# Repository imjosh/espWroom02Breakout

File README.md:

# espWroom02Breakout
Breakout board for the ESPWROOM02 Esp8266 Module

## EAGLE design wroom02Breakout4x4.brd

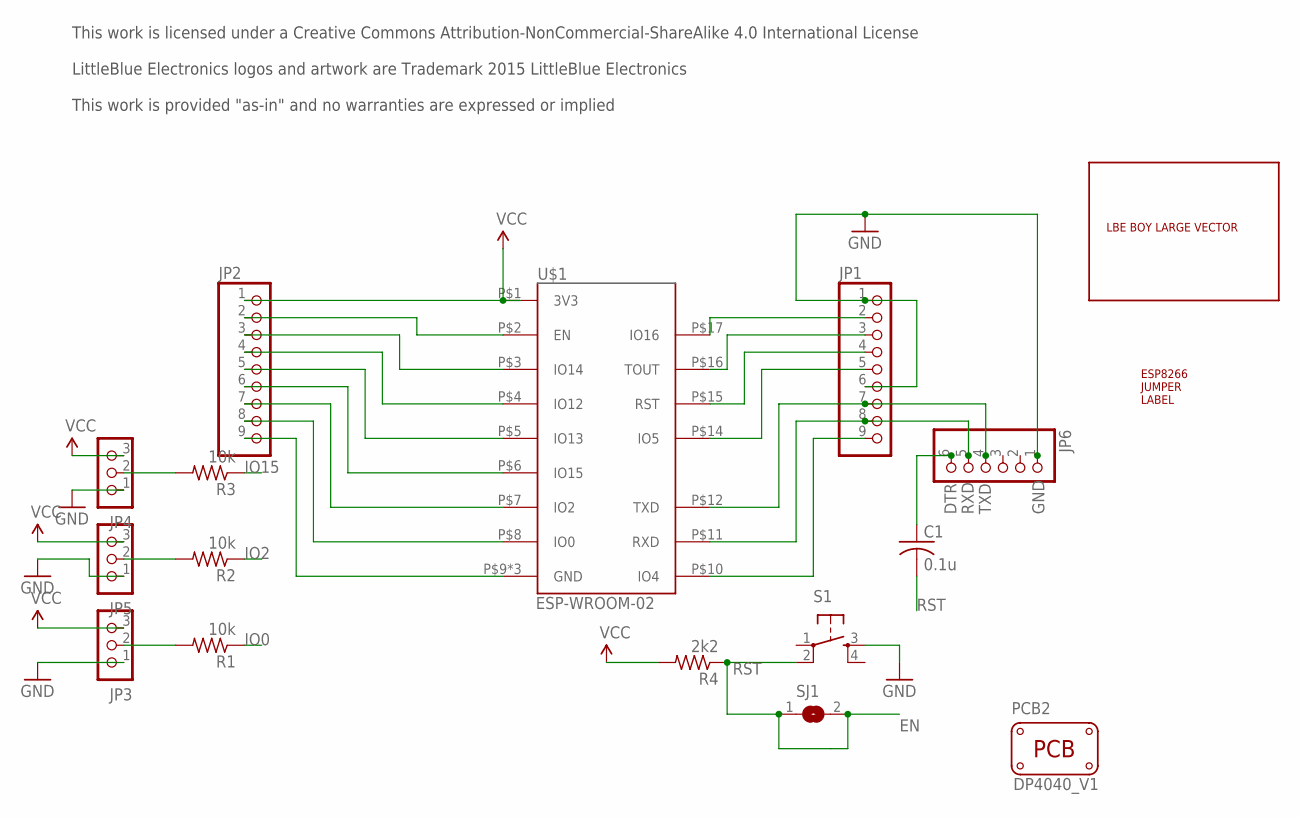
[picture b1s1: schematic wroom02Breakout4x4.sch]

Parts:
C1: 0.1u; C0603
JP1, JP2: PINHD-1X9; 1X09
JP3, JP4, JP5: CON_HEADER_1X03-PTH; M1X3
JP6: PINHD-1X6/90; 1X06/90
PCB2: PCB_DP_SQUARE-4X4; DP4040_V1
R1, R2, R3: 10k; R0603
R4: 2k2; R0603
S1: TAC_SWITCHSMD; TACTILE_SWITCH_SMD
SJ1: SJ
U$1: ESP-WROOM-02
U$4: LBE-BOY-LARGE-VECTOR; LBE_BOY_LARGE_VECTOR
U$5: ESP8266_JUMPER_LABEL

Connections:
DTR: C1.1, JP6.6
EN: JP2.2, SJ1.2, U$1.P$2 (EN)
GND: JP1.1, JP1.6, JP2.9, JP3.1, JP4.1, JP5.1, JP6.1, S1.3, U$1.P$9 (GND), U$1.P$13 (GND), U$1.P$18 (GND)
IO0: JP2.8, R1.1, U$1.P$8 (IO0)
IO2: JP2.7, R2.1, U$1.P$7 (IO2)
IO4: JP1.9, U$1.P$10 (IO4)
IO5: JP1.5, U$1.P$14 (IO5)
IO12: JP2.4, U$1.P$4 (IO12)
IO13: JP2.5, U$1.P$5 (IO13)
IO14: JP2.3, U$1.P$3 (IO14)
IO15: JP2.6, R3.1, U$1.P$6 (IO15)
IO16: JP1.2, U$1.P$17 (IO16)
unnamed: JP3.2, R1.2
unnamed: JP5.2, R2.2
unnamed: JP4.2, R3.2
RST: C1.2, JP1.4, R4.1, S1.2, SJ1.1, U$1.P$15 (RST)
RXD: JP1.8, JP6.5, U$1.P$11 (RXD)
TOUT: JP1.3, U$1.P$16 (TOUT)
TXD: JP1.7, JP6.4, U$1.P$12 (TXD)
VCC: JP2.1, JP3.3, JP4.3, JP5.3, R4.2, U$1.P$1 (3V3)

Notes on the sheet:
This work is licensed under a Creative Commons Attribution-NonCommercial-ShareAlike 4.0 International License LittleBlue Electronics logos and artwork are Trademark 2015 LittleBlue Electronics This work is provided "as-in" and no warranties are expressed or implied

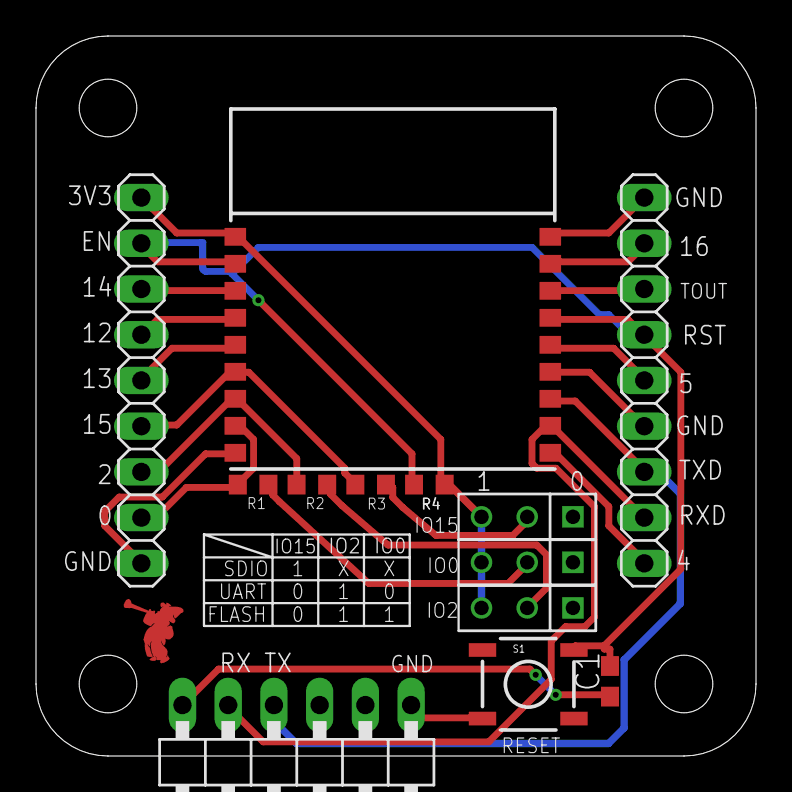
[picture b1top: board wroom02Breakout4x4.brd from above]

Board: 2 copper layers, 40.0 x 40.0 mm, 18 parts (1 on the bottom side), 20 nets.

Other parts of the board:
U$2: LBE-BOY-SM-VECTOR; LBE_BOY_SMALL_VECTOR

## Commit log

2015-10-09 Initial commit - current brd is untested YMMV

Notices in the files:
parts and their libraries:
SparkFun-Electromechanical: Licensing: CC v3.0 Share-Alike You are welcome to use this library for commercial purposes.
